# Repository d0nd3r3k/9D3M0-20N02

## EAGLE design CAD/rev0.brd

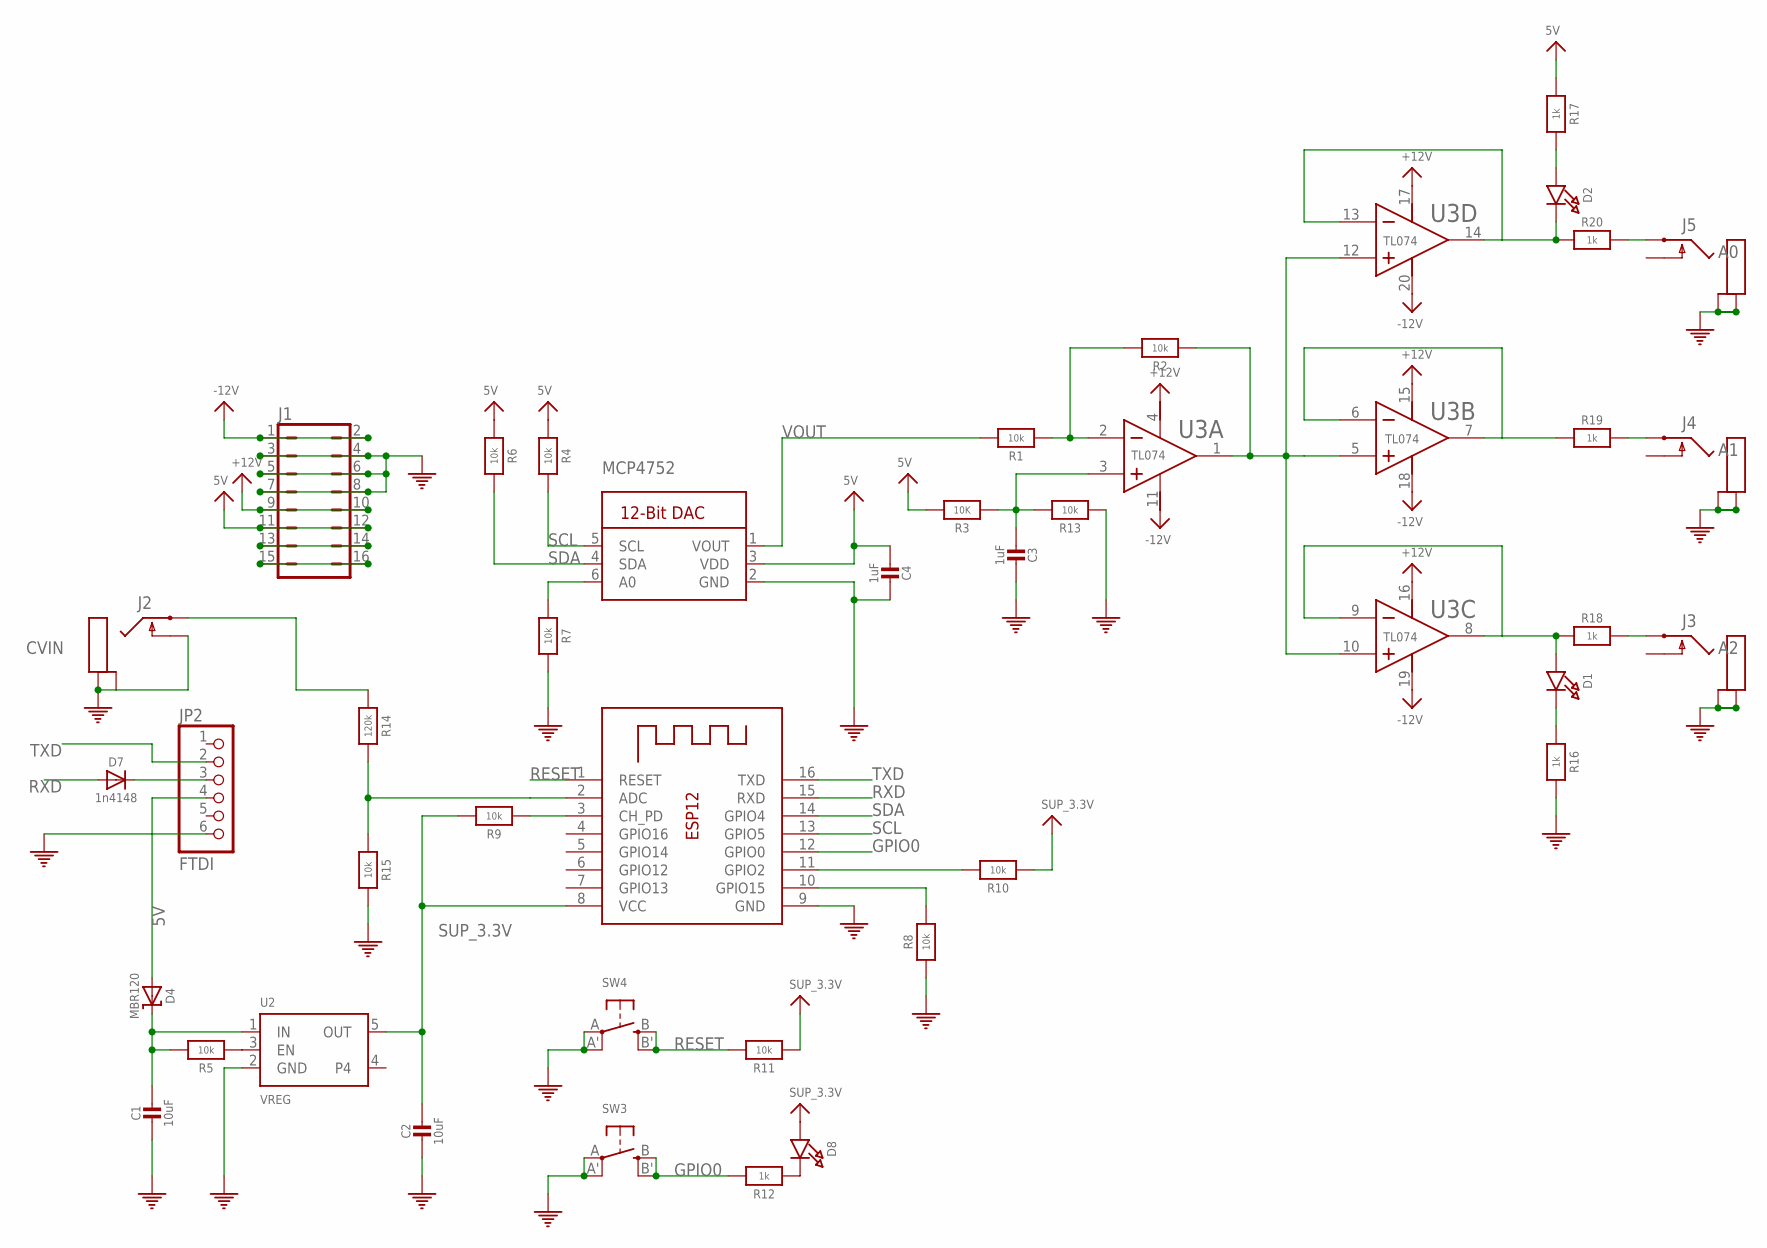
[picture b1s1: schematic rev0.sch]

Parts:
C1, C2: 10uF; 0805-NO
C3, C4: 1uF; 0805
D1, D2, D8: LED0805_NOOUTLINE; CHIPLED_0805_NOOUTLINE
D4: MBR120; SOD-123
D7: 1n4148; SOD-323
J1: JMP/16P/DIPDIP; JMP/16P/DIP
J2, J3, J4, J5: 1/8"JACK/MONO/SWITCHED; 1/8"JACK/MONO/ERTHENVAR
JP2: FTDI; 1X06_ROUND_70
MCP4752: DAC_MCP4725; SOT23-6
R1, R2, R4, R5, R6, R7, R8, R9, R10, R11, R13, R15: 10k; 0805-NO
R3: 10K; 0805-NO
R12, R16, R17, R18, R19, R20: 1k; 0805-NO
R14: 120k; 0805-NO
SW3, SW4: SWITCH_TACT_SMT4.6X2.8; BTN_KMR2_4.6X2.8
U2: VREG; SOT23-5
U3: TEXAS_INSTRUMENTS_TL074CDRTEXAS_INSTRUMENTS_TL074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; TEXAS_INSTRUMENTS_TL074CDR_0
X1: ESP-12

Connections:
5V: C4.1, D4.A, J1.11, J1.12, JP2.4, MCP4752.3 (VDD), R3.2, R4.1, R6.1, R17.1
+12V: J1.9, J1.10, U3.4 (VCC+), U3.15 (VCC+), U3.16 (VCC+), U3.17 (VCC+)
-12V: J1.1, J1.2, U3.11 (VCC-), U3.18 (VCC-), U3.19 (VCC-), U3.20 (VCC-)
A0: D2.C, R20.1, U3.13 (IN4-), U3.14 (OUT4)
A1: R19.1, U3.6 (IN2-), U3.7 (OUT2)
A2: D1.A, R18.1, U3.8 (OUT3), U3.9 (IN3-)
CVIN: J2.P$1 (5), R14.1
CVOUT: R2.1, U3.1 (OUT1), U3.5 (IN2+), U3.10 (IN3+), U3.12 (IN4+)
GND: C1.2, C2.2, C3.2, C4.2, J1.3, J1.4, J1.5, J1.6, J1.7, J1.8, J2.P$2 (4), J2.P$3 (1), J2.P$4, J3.P$3 (1), J3.P$4, J4.P$3 (1), J4.P$4, J5.P$3 (1), J5.P$4, JP2.6, MCP4752.2 (GND), R7.2, R8.1, R13.1, R15.2, R16.2, SW3.A, SW3.A' (P1), SW4.A, SW4.A' (P1), U2.2 (GND), X1.9 (GND)
GPIO0: R12.2, SW3.B (S), SW3.B' (S1), X1.12 (GPIO0)
GPIO15: R8.2, X1.10 (GPIO15)
I0: R14.2, R15.1, X1.2 (ADC)
unnamed: R1.1, R2.2, U3.2 (IN1-)
unnamed: J5.P$1 (5), R20.2
unnamed: D8.C, R12.1
unnamed: R5.1, U2.3 (EN)
unnamed: D7.C, JP2.3
unnamed: C1.1, D4.C, R5.2, U2.1 (IN)
unnamed: MCP4752.6 (A0), R7.1
unnamed: R10.2, X1.11 (GPIO2)
unnamed: R9.1, X1.3 (CH_PD)
unnamed: J4.P$1 (5), R19.2
unnamed: J3.P$1 (5), R18.2
unnamed: C3.1, R3.1, R13.2, U3.3 (IN1+)
unnamed: D1.C, R16.1
unnamed: D2.A, R17.2
unnamed: J1.13, J1.14
unnamed: J1.15, J1.16
RESET: R11.2, SW4.B (S), SW4.B' (S1), X1.1 (RESET)
RXD: D7.A, X1.15 (RXD)
SCL: MCP4752.5 (SCL), R4.2, X1.13 (GPIO5)
SDA: MCP4752.4 (SDA), R6.2, X1.14 (GPIO4)
SUP_3.3V: C2.1, D8.A, R9.2, R10.1, R11.1, U2.5 (OUT), X1.8 (VCC)
TXD: JP2.2, X1.16 (TXD)
VOUT: MCP4752.1 (VOUT), R1.2

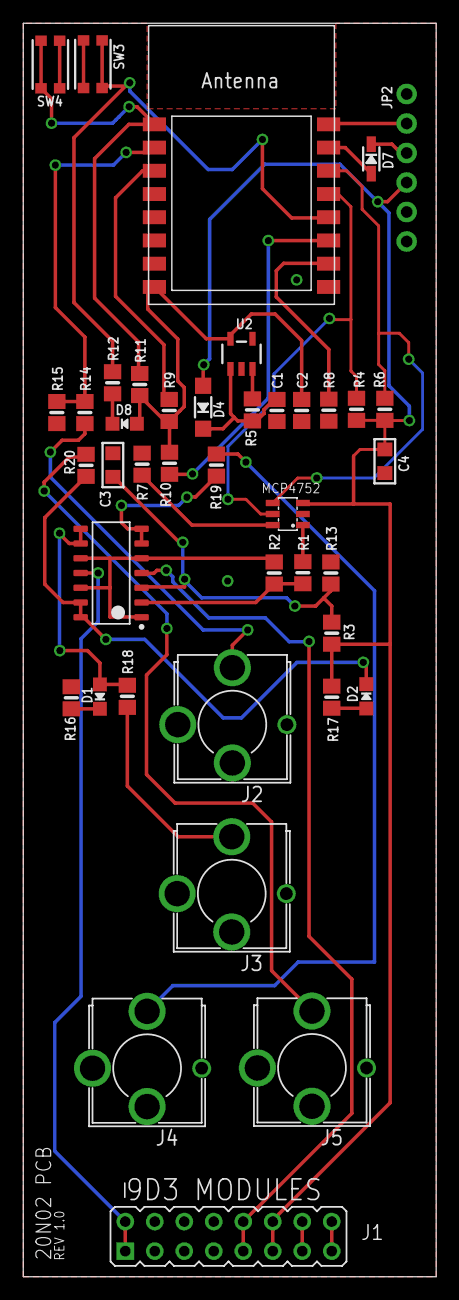
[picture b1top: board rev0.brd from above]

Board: 2 copper layers, 35.6 x 108.0 mm, 41 parts (0 on the bottom side), 35 nets.

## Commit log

2019-04-01 second commit
